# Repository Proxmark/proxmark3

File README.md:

# proxmark3: the official Proxmark repository!

The proxmark3 is a powerful general purpose RFID tool, the size of a deck
of cards, designed to snoop, listen and emulate everything from
**Low Frequency (125kHz)** to **High Frequency (13.56MHz)** tags.

This repository contains enough software, logic (for the FPGA), and design
documentation for the hardware that you could, at least in theory,
do something useful with a proxmark3.

## Resources

* [This repository!](https://github.com/Proxmark/proxmark3)
* [The Wiki](https://github.com/Proxmark/proxmark3/wiki)
* [The GitHub Pages website](http://proxmark.github.io/proxmark3/)
* [The Forum](http://www.proxmark.org/forum)
* The IRC channel: irc.freenode.org #proxmark3 ([chat in your browser](http://webchat.freenode.net/?channels=#proxmark3))
* [The Homebrew formula repository](https://github.com/Proxmark/homebrew-proxmark3)
* [Proxmark3 community discord server](https://discord.gg/86VcRtS)
   
## Development

The tools required to build  or run the project will vary depending on
your operating system. Please refer to [the wiki](https://github.com/Proxmark/proxmark3/wiki) for details.

## Obtaining hardware

The Proxmark3 is available for purchase (assembled and tested) from the
following locations:

| Distributor Name | Warehouse Location | Entity Location |
|------------------|--------------------|-----------------|
| [RyscCorp](https://proxmark3.com/)         | USA                | USA             |
| [Hackerwarehouse](https://hackerwarehouse.com/)  | USA                | USA             |
| [Elechouse](http://www.elechouse.com/)        | HK                 | HK              |
| [Lab401](https://lab401.com/)           | EU                 | HK              |
| [RFxSecure](http://www.rfxsecure.com/)       | CN                 | SG              |
| [Sneaktechnology](https://www.sneaktechnology.com/)  | CN                 | CN              |

Most of the ultra-low-volume contract assemblers could put
something like this together with a reasonable yield. A run of around
a dozen units is probably cost-effective. The BOM includes (possibly-
outdated) component pricing, and everything is available from Digikey
and the usual distributors.

If you've never assembled a modern circuit board by hand, then this is
not a good place to start. Some of the components (e.g. the crystals)
must not be assembled with a soldering iron, and require hot air.

The schematics are included; the component values given are not
necessarily correct for all situations, but it should be possible to do
nearly anything you would want with appropriate population options.

The printed circuit board artwork is also available, as Gerbers and an
Excellon drill file.

## License

This program is free software; you can redistribute it and/or modify
it under the terms of the GNU General Public License as published by
the Free Software Foundation; either version 2 of the License, or
(at your option) any later version.

This program is distributed in the hope that it will be useful,
but WITHOUT ANY WARRANTY; without even the implied warranty of
MERCHANTABILITY or FITNESS FOR A PARTICULAR PURPOSE.  See the
GNU General Public License for more details.

You should have received a copy of the GNU General Public License
along with this program; if not, write to the Free Software
Foundation, Inc., 51 Franklin St, Fifth Floor, Boston, MA  02110-1301  USA

Jonathan Westhues
user jwesthues, at host cq.cx

May 2007, Cambridge MA

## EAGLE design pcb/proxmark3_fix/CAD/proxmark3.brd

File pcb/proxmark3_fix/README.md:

Corrected Eagle layout files and re-generated CAM files. DRC checked (via eurocircuits.com 's PCB visualizer too) no problems found, ready to production!

Please find the change list in the CAD folder text file.

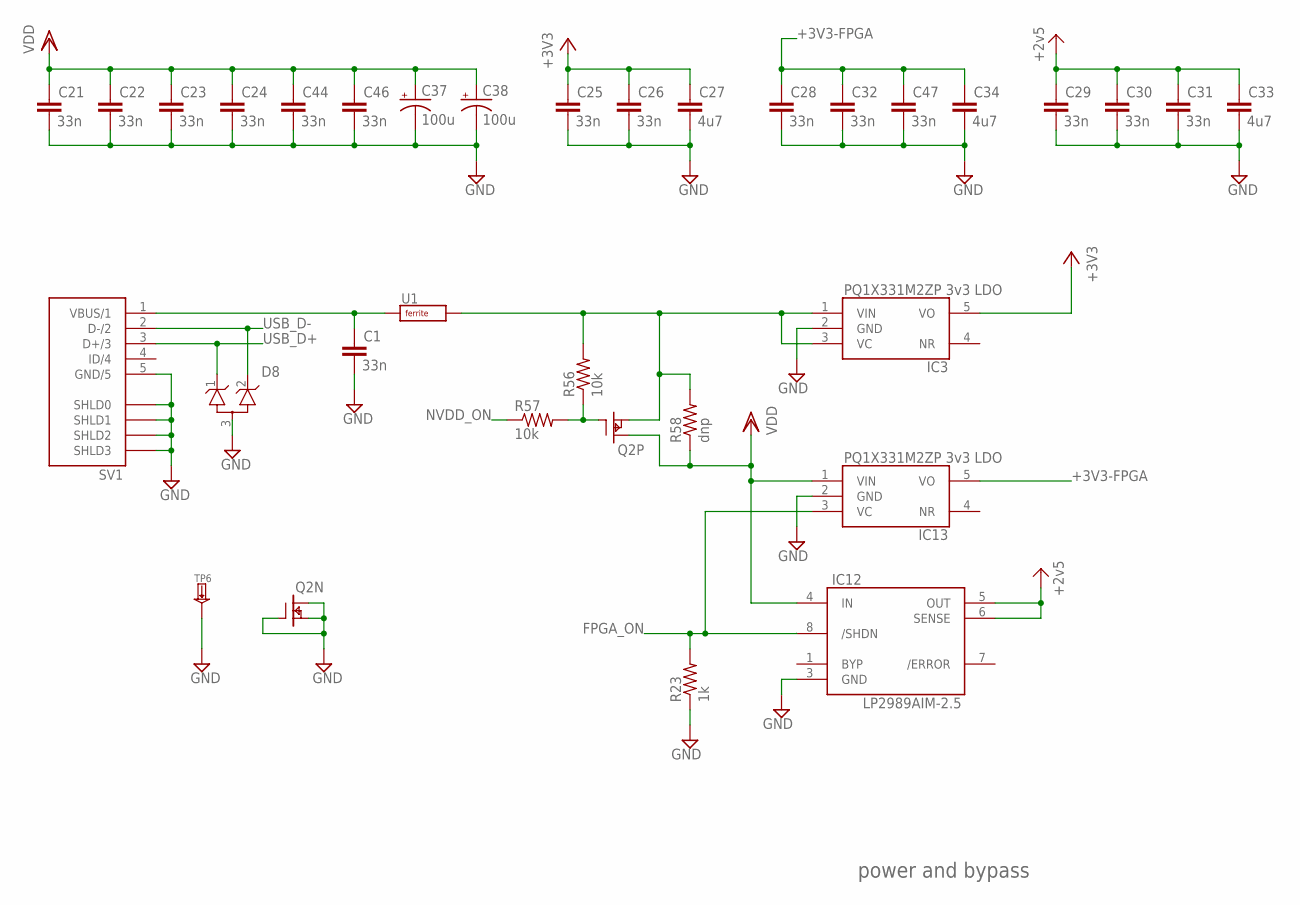
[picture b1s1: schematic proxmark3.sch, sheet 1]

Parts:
C1, C21, C22, C23, C24, C25, C26, C28, C29, C30, C31, C32, C44, C46, C47: 33n; RLC_0603
C27, C33, C34: 4u7; RLC_1210
C37, C38: 100u; CAPCAITOR-ELECTROLYTIC-ALCHIP-MZA-F80
D8: --MERGED_DUAL-TVS-COMMON-ANODE; --MERGED_SOT23-3LEAD
IC3, IC13: --MERGED_PQ1X331M2ZP-3V3-LDO-SOT-23-5; --MERGED_SOT-23-5
IC12: LP2989AIM-2.5; SOIC-8
Q2: IRF7307; SOIC-8
R23: 1k; RLC_0603
R56, R57: 10k; RLC_0603
R58: dnp; RLC_0603
SV1: USB-MINIB; USB-MINIB-SMD
TP6: TESTPADKEYSTONE-PTH; KEYSTONE-PTH-TESTPOINT-5011
U1: FERRITE0805; RLC_0805

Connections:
+2V5: C29.1, C30.1, C31.1, C33.1, IC12.5 (OUT), IC12.6 (SENSE); also elsewhere on the board
+3V3: C25.1, C26.1, C27.1, IC3.5 (VO); also elsewhere on the board
+3V3-FPGA: C28.1, C32.1, C34.1, C47.1, IC13.5 (VO); also elsewhere on the board
FPGA_ON: IC12.8 (/SHDN), IC13.3 (VC), R23.2; also elsewhere on the board
GND: C1.2, C21.2, C22.2, C23.2, C24.2, C25.2, C26.2, C27.2, C28.2, C29.2, C30.2, C31.2, C32.2, C33.2, C34.2, C37.-, C38.-, C44.2, C46.2, C47.2, D8.3 (A), IC3.2 (GND), IC12.3 (GND), IC13.2 (GND), Q2.1 (S), Q2.2 (G), Q2.8 (D), R23.1, SV1.5 (GND/5), SV1.TAB0 (SHLD0), SV1.TAB1 (SHLD1), SV1.TAB2 (SHLD2), SV1.TAB3 (SHLD3), TP6.A; also elsewhere on the board
unnamed: C1.1, SV1.1 (VBUS/1), U1.1 (A)
unnamed: IC3.1 (VIN), IC3.3 (VC), Q2.3 (S), R56.2, R58.2, U1.2 (B)
NVDD_ON: R57.1; also elsewhere on the board
PFETGATE: Q2.4 (G), R56.1, R57.2
USB_D+: D8.1 (K1), SV1.3 (D+/3); also elsewhere on the board
USB_D-: D8.2 (K2), SV1.2 (D-/2); also elsewhere on the board
VDD: C21.1, C22.1, C23.1, C24.1, C37.+, C38.+, C44.1, C46.1, IC12.4 (IN), IC13.1 (VIN), Q2.6 (D), R58.1; also elsewhere on the board

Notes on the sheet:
power and bypass

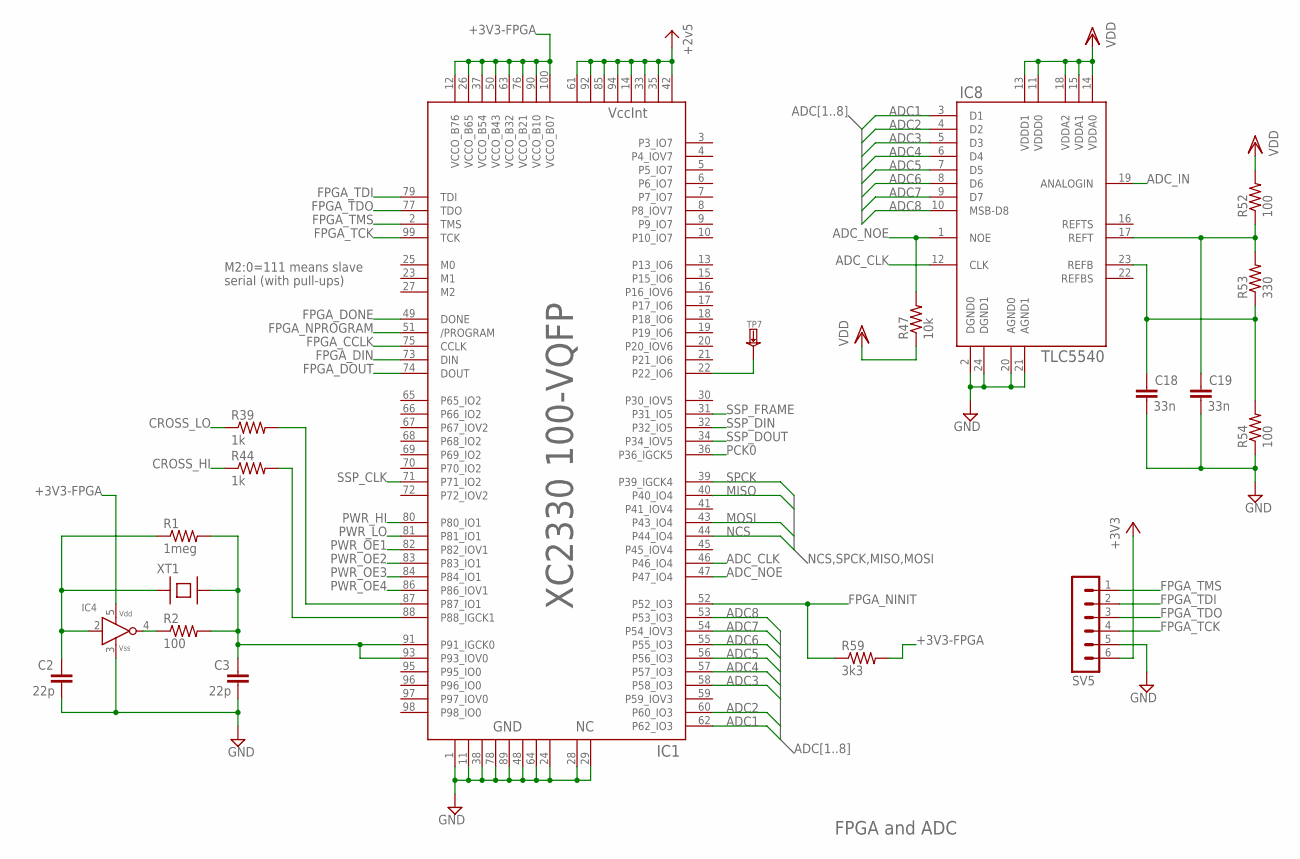
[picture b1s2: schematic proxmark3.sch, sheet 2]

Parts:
C2, C3: 22p; RLC_0603
C18, C19: 33n; RLC_0603
IC1: SPARTAN-II-XC2S30-100-VQFP; VQFP-100
IC4: HCU-INVERTER; SMV-5
IC8: TLC5540; TSSOP-24
R1: 1meg; RLC_0603
R2, R52, R54: 100; RLC_0603
R39, R44: 1k; RLC_0603
R47: 10k; RLC_0603
R53: 330; RLC_0603
R59: 3k3; RLC_0603
SV5: --MERGED_HEADER-MALE-6X1; --MERGED_HEADER-MALE-6X1-0.100-UNKEYED
TP7: TESTPADKEYSTONE-SMD; KEYSTONE-SMD-TESTPOINT-5015
XT1: XTAL-SMD-CITIZEN-CS10

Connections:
+2V5: IC1.14 (VCCINT5), IC1.33 (VCCINT6), IC1.35 (VCCINT7), IC1.42 (VCCINT8), IC1.61 (VCCINT1), IC1.85 (VCCINT3), IC1.92 (VCCINT2), IC1.94 (VCCINT4); also elsewhere on the board
+3V3: SV5.6; also elsewhere on the board
+3V3-FPGA: IC1.12 (VCCO_B76), IC1.26 (VCCO_B65), IC1.37 (VCCO_B54), IC1.50 (VCCO_B43), IC1.63 (VCCO_B32), IC1.76 (VCCO_B21), IC1.90 (VCCO_B10), IC1.100 (VCCO_B07), IC4.5 (VDD), R59.2; also elsewhere on the board
ADC1: IC1.62 (P62_IO3), IC8.3 (D1)
ADC2: IC1.60 (P60_IO3), IC8.4 (D2)
ADC3: IC1.58 (P58_IO3), IC8.5 (D3)
ADC4: IC1.57 (P57_IO3), IC8.6 (D4)
ADC5: IC1.56 (P56_IO3), IC8.7 (D5)
ADC6: IC1.55 (P55_IO3), IC8.8 (D6)
ADC7: IC1.54 (P54_IOV3), IC8.9 (D7)
ADC8: IC1.53 (P53_IO3), IC8.10 (MSB-D8)
ADC_CLK: IC1.46 (P46_IO4), IC8.12 (CLK)
ADC_IN: IC8.19 (ANALOGIN); also elsewhere on the board
ADC_NOE: IC1.47 (P47_IO4), IC8.1 (NOE), R47.2
CROSS_HI: R44.1; also elsewhere on the board
CROSS_LO: R39.1; also elsewhere on the board
FPGA_CCLK: IC1.75 (CCLK); also elsewhere on the board
FPGA_DIN: IC1.73 (DIN); also elsewhere on the board
FPGA_DONE: IC1.49 (DONE); also elsewhere on the board
FPGA_DOUT: IC1.74 (DOUT); also elsewhere on the board
FPGA_NINIT: IC1.52 (P52_IO3), R59.1; also elsewhere on the board
FPGA_NPROGRAM: IC1.51 (/PROGRAM); also elsewhere on the board
FPGA_TCK: IC1.99 (TCK), SV5.4
FPGA_TDI: IC1.79 (TDI), SV5.2
FPGA_TDO: IC1.77 (TDO), SV5.3
FPGA_TMS: IC1.2 (TMS), SV5.1
GND: C2.2, C3.2, C18.2, C19.2, IC1.1 (GND1), IC1.11 (GND2), IC1.24 (GND8), IC1.28 (NC0), IC1.29 (NC1), IC1.38 (GND3), IC1.48 (GND6), IC1.64 (GND7), IC1.78 (GND4), IC1.89 (GND5), IC4.3 (VSS), IC8.2 (DGND0), IC8.20 (AGND0), IC8.21 (AGND1), IC8.24 (DGND1), R54.1, SV5.5; also elsewhere on the board
MISO: IC1.40 (P40_IO4); also elsewhere on the board
MOSI: IC1.43 (P43_IO4); also elsewhere on the board
unnamed: IC4.4 (Y), R2.1
unnamed: C2.1, IC4.2 (A), R1.1, XT1.A
unnamed: C3.1, IC1.91 (P91_IGCK0), IC1.93 (P93_IOV0), R1.2, R2.2, XT1.B
unnamed: C18.1, IC8.23 (REFB), R53.1, R54.2
unnamed: IC1.87 (P87_IO1), R39.2
unnamed: IC1.88 (P88_IGCK1), R44.2
unnamed: C19.1, IC8.17 (REFT), R52.1, R53.2
unnamed: IC1.22 (P22_IO6), TP7.1
NCS: IC1.44 (P44_IO4); also elsewhere on the board
PCK0: IC1.36 (P36_IGCK5); also elsewhere on the board
PWR_HI: IC1.80 (P80_IO1); also elsewhere on the board
PWR_LO: IC1.81 (P81_IO1); also elsewhere on the board
PWR_OE1: IC1.82 (P82_IOV1); also elsewhere on the board
PWR_OE2: IC1.83 (P83_IO1); also elsewhere on the board
PWR_OE3: IC1.84 (P84_IO1); also elsewhere on the board
PWR_OE4: IC1.86 (P86_IOV1); also elsewhere on the board
SPCK: IC1.39 (P39_IGCK4); also elsewhere on the board
SSP_CLK: IC1.71 (P71_IO2); also elsewhere on the board
SSP_DIN: IC1.32 (P32_IO5); also elsewhere on the board
SSP_DOUT: IC1.34 (P34_IOV5); also elsewhere on the board
SSP_FRAME: IC1.31 (P31_IO5); also elsewhere on the board
VDD: IC8.11 (VDDD0), IC8.13 (VDDD1), IC8.14 (VDDA0), IC8.15 (VDDA1), IC8.18 (VDDA2), R47.1, R52.2; also elsewhere on the board

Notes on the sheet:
FPGA and ADC
M2:0=111 means slave
serial (with pull-ups)

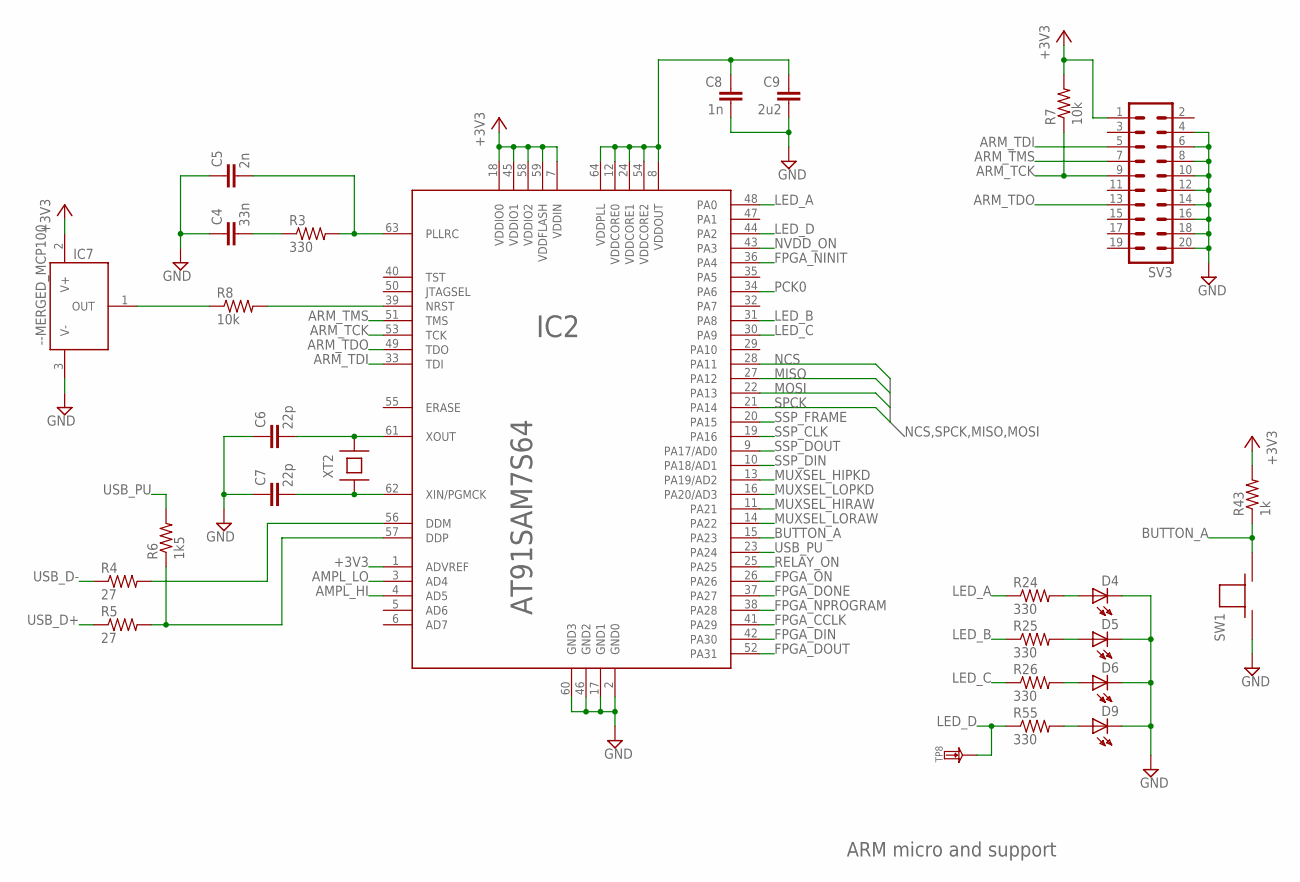
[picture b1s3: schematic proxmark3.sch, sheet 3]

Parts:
C4: 33n; RLC_0603
C5: 2n; RLC_0603
C6, C7: 22p; --MERGED_RLC_0603
C8: 1n; RLC_0603
C9: 2u2; RLC_1210
D4, D5, D6, D9: LED; LED_0603
IC2: AT91SAM7S64; LQFP-64
IC7: --MERGED_MCP100; --MERGED_SOT23-3LEAD
R3, R24, R25, R26, R55: 330; RLC_0603
R4, R5: 27; RLC_0603
R6: 1k5; RLC_0603
R7, R8: 10k; RLC_0603
R43: 1k; RLC_0603
SV3: HEADER-MALE-10X2; HEADER-MALE-10X2-0.100-SHROUDED
SW1: TACTSWITCH; TACTSWITCH-SMD-EVQQ1
TP8: TESTPADKEYSTONE-SMD; KEYSTONE-SMD-TESTPOINT-5015
XT2: XTAL-SMD-CITIZEN-CS10

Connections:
+3V3: IC2.1 (ADVREF), IC2.7 (VDDIN), IC2.18 (VDDIO0), IC2.45 (VDDIO1), IC2.58 (VDDIO2), IC2.59 (VDDFLASH), IC7.2 (V+), R7.2, R43.2, SV3.1; also elsewhere on the board
AMPL_HI: IC2.4 (AD5); also elsewhere on the board
AMPL_LO: IC2.3 (AD4); also elsewhere on the board
ARM_TCK: IC2.53 (TCK), R7.1, SV3.9
ARM_TDI: IC2.33 (TDI), SV3.5
ARM_TDO: IC2.49 (TDO), SV3.13
ARM_TMS: IC2.51 (TMS), SV3.7
BUTTON_A: IC2.15 (PA23), R43.1, SW1.B
FPGA_CCLK: IC2.41 (PA29); also elsewhere on the board
FPGA_DIN: IC2.42 (PA30); also elsewhere on the board
FPGA_DONE: IC2.37 (PA27); also elsewhere on the board
FPGA_DOUT: IC2.52 (PA31); also elsewhere on the board
FPGA_NINIT: IC2.36 (PA4); also elsewhere on the board
FPGA_NPROGRAM: IC2.38 (PA28); also elsewhere on the board
FPGA_ON: IC2.26 (PA26); also elsewhere on the board
GND: C4.1, C5.1, C6.1, C7.1, C8.2, C9.2, D4.- (C), D5.- (C), D6.- (C), D9.- (C), IC2.2 (GND0), IC2.17 (GND1), IC2.46 (GND2), IC2.60 (GND3), IC7.3 (V-), SV3.4, SV3.6, SV3.8, SV3.10, SV3.12, SV3.14, SV3.16, SV3.18, SV3.20, SW1.A; also elsewhere on the board
LED_A: IC2.48 (PA0), R24.1
LED_B: IC2.31 (PA8), R25.1
LED_C: IC2.30 (PA9), R26.1
LED_D: IC2.44 (PA2), R55.1, TP8.1
MISO: IC2.27 (PA12); also elsewhere on the board
MOSI: IC2.22 (PA13); also elsewhere on the board
MUXSEL_HIPKD: IC2.13 (PA19/AD2); also elsewhere on the board
MUXSEL_HIRAW: IC2.11 (PA21); also elsewhere on the board
MUXSEL_LOPKD: IC2.16 (PA20/AD3); also elsewhere on the board
MUXSEL_LORAW: IC2.14 (PA22); also elsewhere on the board
unnamed: C5.2, IC2.63 (PLLRC), R3.2
unnamed: C4.2, R3.1
unnamed: C6.2, IC2.61 (XOUT), XT2.B
unnamed: C7.2, IC2.62 (XIN/PGMCK), XT2.A
unnamed: IC2.39 (NRST), R8.2
unnamed: C8.1, C9.1, IC2.8 (VDDOUT), IC2.12 (VDDCORE0), IC2.24 (VDDCORE1), IC2.54 (VDDCORE2), IC2.64 (VDDPLL)
unnamed: IC2.56 (DDM), R4.2
unnamed: IC2.57 (DDP), R5.2, R6.1
unnamed: IC7.1 (OUT), R8.1
unnamed: D9.+ (A), R55.2
unnamed: D6.+ (A), R26.2
unnamed: D5.+ (A), R25.2
unnamed: D4.+ (A), R24.2
NCS: IC2.28 (PA11); also elsewhere on the board
NVDD_ON: IC2.43 (PA3); also elsewhere on the board
PCK0: IC2.34 (PA6); also elsewhere on the board
RELAY_ON: IC2.25 (PA25); also elsewhere on the board
SPCK: IC2.21 (PA14); also elsewhere on the board
SSP_CLK: IC2.19 (PA16); also elsewhere on the board
SSP_DIN: IC2.10 (PA18/AD1); also elsewhere on the board
SSP_DOUT: IC2.9 (PA17/AD0); also elsewhere on the board
SSP_FRAME: IC2.20 (PA15); also elsewhere on the board
USB_D+: R5.1; also elsewhere on the board
USB_D-: R4.1; also elsewhere on the board
USB_PU: IC2.23 (PA24), R6.2

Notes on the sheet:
ARM micro and support

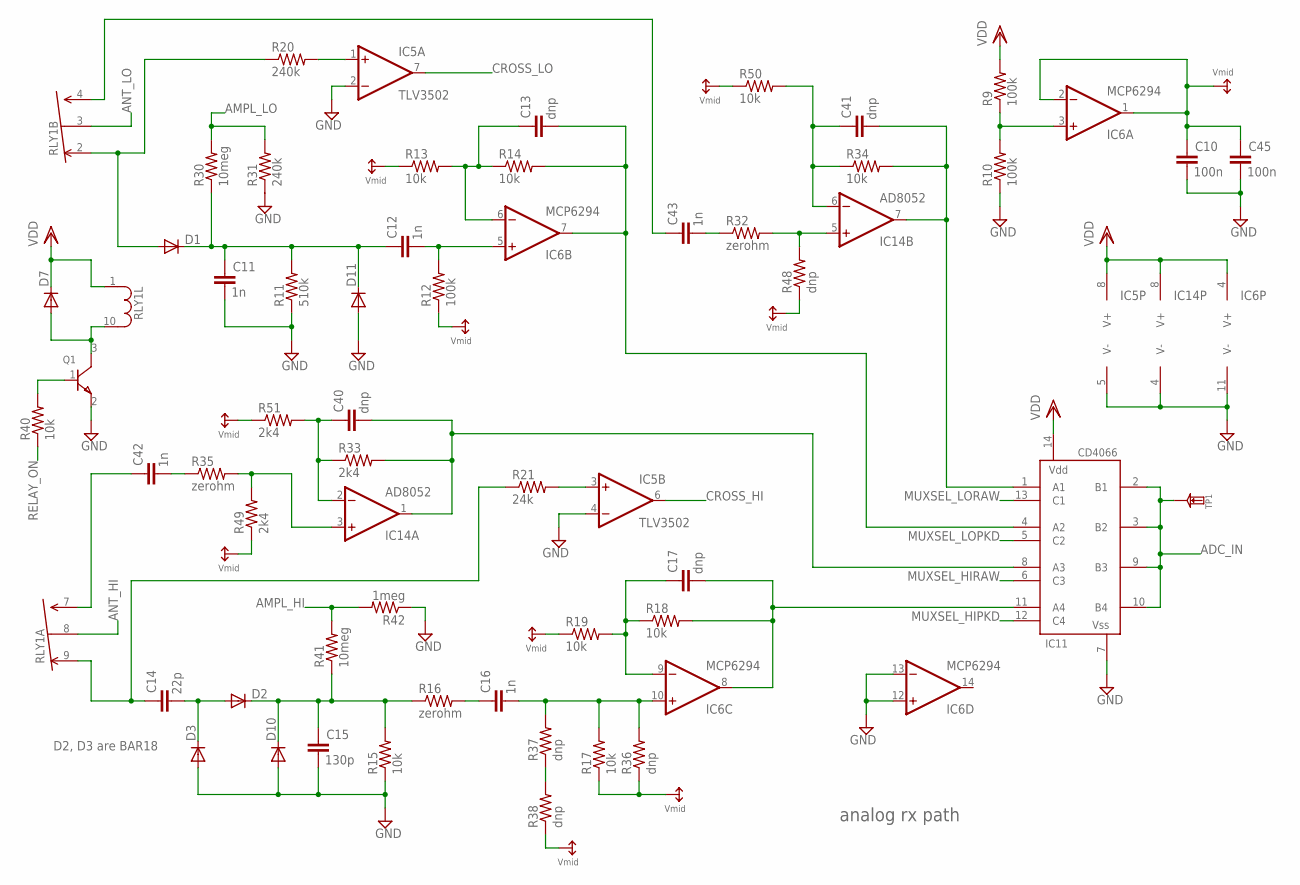
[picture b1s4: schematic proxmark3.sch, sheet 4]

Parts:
C10, C45: 100n; RLC_0603
C11, C12, C16, C42, C43: 1n; RLC_0603
C13, C17, C40, C41: dnp; RLC_0603
C14: 22p; RLC_0603
C15: 130p; RLC_0603
D1, D2, D3, D7, D10, D11: --MERGED_DIODE-SMD-SOT23; --MERGED_SOT23-3LEAD
IC5: TLV3502; SOT-23-8-OR-MSOP-8
IC6: MCP6294; TSSOP-14
IC11: CD4066; TSSOP-14
IC14: AD8052; MSOP8
Q1: --MERGED_NPN-SOT23-2N3904; --MERGED_SOT23-3LEAD
R9, R10, R12: 100k; RLC_0603
R11: 510k; RLC_0603
R13, R14, R15, R17, R18, R19, R34, R40, R50: 10k; RLC_0603
R16, R32, R35: zerohm; RLC_0603
R20, R31: 240k; RLC_0603
R21: 24k; RLC_0603
R30, R41: 10meg; RLC_0603
R33, R49, R51: 2k4; RLC_0603
R36, R37, R38, R48: dnp; RLC_0603
R42: 1meg; RLC_0603
RLY1: --MERGED_RELAY-DPDT; --MERGED_TQ-SMD-RELAY
TP1: TESTPADKEYSTONE-SMD; KEYSTONE-SMD-TESTPOINT-5015

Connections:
ADCDR_HI: C17.2, IC6.8 (OUT), IC11.11 (A4), R18.2
ADCDR_LO: C13.2, IC6.7 (OUT), IC11.4 (A2), R14.2
ADC_IN: IC11.2 (B1), IC11.3 (B2), IC11.9 (B3), IC11.10 (B4), TP1.1; also elsewhere on the board
AMPL_HI: R41.2, R42.2; also elsewhere on the board
AMPL_LO: R30.2, R31.2; also elsewhere on the board
ANT_HI: RLY1.8 (COM); also elsewhere on the board
ANT_LO: RLY1.3 (COM); also elsewhere on the board
CROSS_HI: IC5.6 (OUT); also elsewhere on the board
CROSS_LO: IC5.7 (OUT); also elsewhere on the board
GND: C10.2, C11.2, C15.2, C45.2, D3.1 (A), D10.1 (A), D11.1 (A), IC5.2 (-IN), IC5.4 (-IN), IC5.5 (V-), IC6.11 (V-), IC6.12 (+IN), IC6.13 (-IN), IC11.7 (VSS), IC14.4 (V-), Q1.2 (E), R10.1, R11.1, R15.1, R31.1, R42.1; also elsewhere on the board
MUXSEL_HIPKD: IC11.12 (C4); also elsewhere on the board
MUXSEL_HIRAW: IC11.6 (C3); also elsewhere on the board
MUXSEL_LOPKD: IC11.5 (C2); also elsewhere on the board
MUXSEL_LORAW: IC11.13 (C1); also elsewhere on the board
unnamed: IC6.3 (+IN), R9.1, R10.2
unnamed: C17.1, IC6.9 (-IN), R18.1, R19.2
unnamed: C12.2, IC6.5 (+IN), R12.2
unnamed: C13.1, IC6.6 (-IN), R13.2, R14.1
unnamed: C16.1, R16.2
unnamed: C11.1, C12.1, D1.3 (C), D11.3 (C), R11.2, R30.1
unnamed: C14.2, D2.1 (A), D3.3 (C)
unnamed: C15.1, D2.3 (C), D10.3 (C), R15.2, R16.1, R41.1
unnamed: C16.2, IC6.10 (+IN), R17.2, R36.2, R37.2
unnamed: IC5.1 (+IN), R20.2
unnamed: IC5.3 (+IN), R21.2
unnamed: D7.1 (A), Q1.3 (C), RLY1.10
unnamed: C14.1, R21.1, RLY1.9 (NC)
unnamed: C42.1, RLY1.7 (NO)
unnamed: Q1.1 (B), R40.2
unnamed: D1.1 (A), R20.1, RLY1.2 (NC)
unnamed: C41.2, IC11.1 (A1), IC14.7 (OUT), R34.2
unnamed: C43.1, RLY1.4 (NO)
unnamed: IC14.3 (+IN), R35.2, R49.2
unnamed: C43.2, R32.1
unnamed: C42.2, R35.1
unnamed: C40.1, IC14.2 (-IN), R33.1, R51.2
unnamed: C41.1, IC14.6 (-IN), R34.1, R50.2
unnamed: IC14.5 (+IN), R32.2, R48.2
unnamed: R37.1, R38.2
RAW_HI: C40.2, IC11.8 (A3), IC14.1 (OUT), R33.2
RELAY_ON: R40.1; also elsewhere on the board
VDD: D7.3 (C), IC5.8 (V+), IC6.4 (V+), IC11.14 (VDD), IC14.8 (V+), R9.2, RLY1.1; also elsewhere on the board
VMID: C10.1, C45.1, IC6.1 (OUT), IC6.2 (-IN), R12.1, R13.1, R17.1, R19.1, R36.1, R38.1, R48.1, R49.1, R50.1, R51.1

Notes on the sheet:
analog rx path
D2, D3 are BAR18

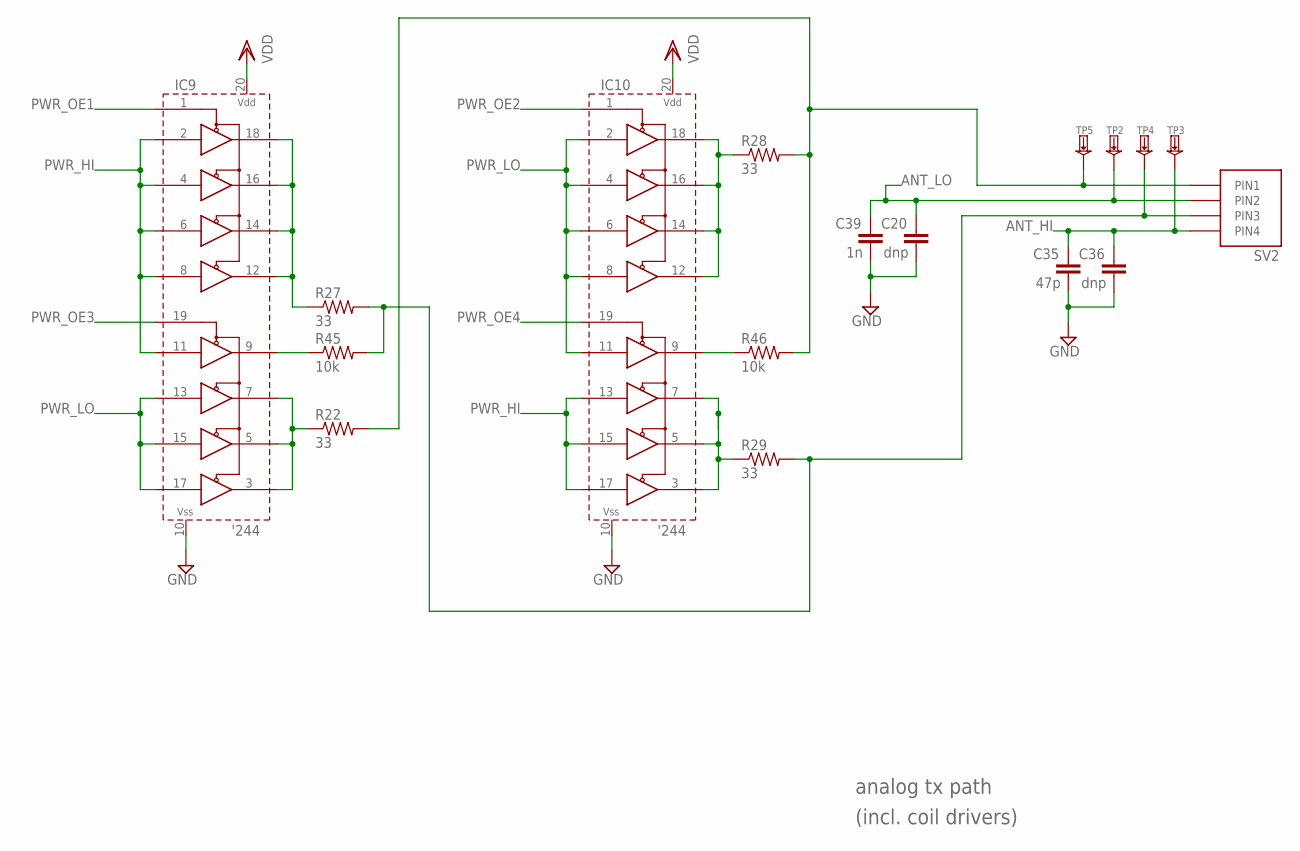
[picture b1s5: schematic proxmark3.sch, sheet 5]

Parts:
C20, C36: dnp; RLC_0603
C35: 47p; RLC_0603
C39: 1n; RLC_0603
IC9, IC10: 74XX244-OCTAL-TRISTATE-BUFFERS; TSSOP-20
R22, R27, R28, R29: 33; RLC_0603
R45, R46: 10k; RLC_0603
SV2: HIROSE-MQ172-4POS
TP2, TP3, TP4, TP5: TESTPADKEYSTONE-SMD; KEYSTONE-SMD-TESTPOINT-5015

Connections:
ANT_HI: C35.1, C36.1, SV2.4 (PIN4), TP3.1; also elsewhere on the board
ANT_LO: C20.1, C39.1, SV2.2 (PIN2), TP2.1; also elsewhere on the board
GND: C20.2, C35.2, C36.2, C39.2, IC9.10 (VSS), IC10.10 (VSS); also elsewhere on the board
unnamed: R27.2, R29.2, R45.2, SV2.3 (PIN3), TP4.1
unnamed: R22.2, R28.2, R46.2, SV2.1 (PIN1), TP5.1
unnamed: IC9.12 (1Y4), IC9.14 (1Y3), IC9.16 (1Y2), IC9.18 (1Y1), R27.1
unnamed: IC10.12 (1Y4), IC10.14 (1Y3), IC10.16 (1Y2), IC10.18 (1Y1), R28.1
unnamed: IC9.3 (2Y4), IC9.5 (2Y3), IC9.7 (2Y2), R22.1
unnamed: IC10.3 (2Y4), IC10.5 (2Y3), IC10.7 (2Y2), R29.1
unnamed: IC9.9 (2Y1), R45.1
unnamed: IC10.9 (2Y1), R46.1
PWR_HI: IC9.2 (1A1), IC9.4 (1A2), IC9.6 (1A3), IC9.8 (1A4), IC9.11 (2A1), IC10.13 (2A2), IC10.15 (2A3), IC10.17 (2A4); also elsewhere on the board
PWR_LO: IC9.13 (2A2), IC9.15 (2A3), IC9.17 (2A4), IC10.2 (1A1), IC10.4 (1A2), IC10.6 (1A3), IC10.8 (1A4), IC10.11 (2A1); also elsewhere on the board
PWR_OE1: IC9.1 (1NOE); also elsewhere on the board
PWR_OE2: IC10.1 (1NOE); also elsewhere on the board
PWR_OE3: IC9.19 (2NOE); also elsewhere on the board
PWR_OE4: IC10.19 (2NOE); also elsewhere on the board
VDD: IC9.20 (VDD), IC10.20 (VDD); also elsewhere on the board

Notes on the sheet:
analog tx path
(incl. coil drivers)

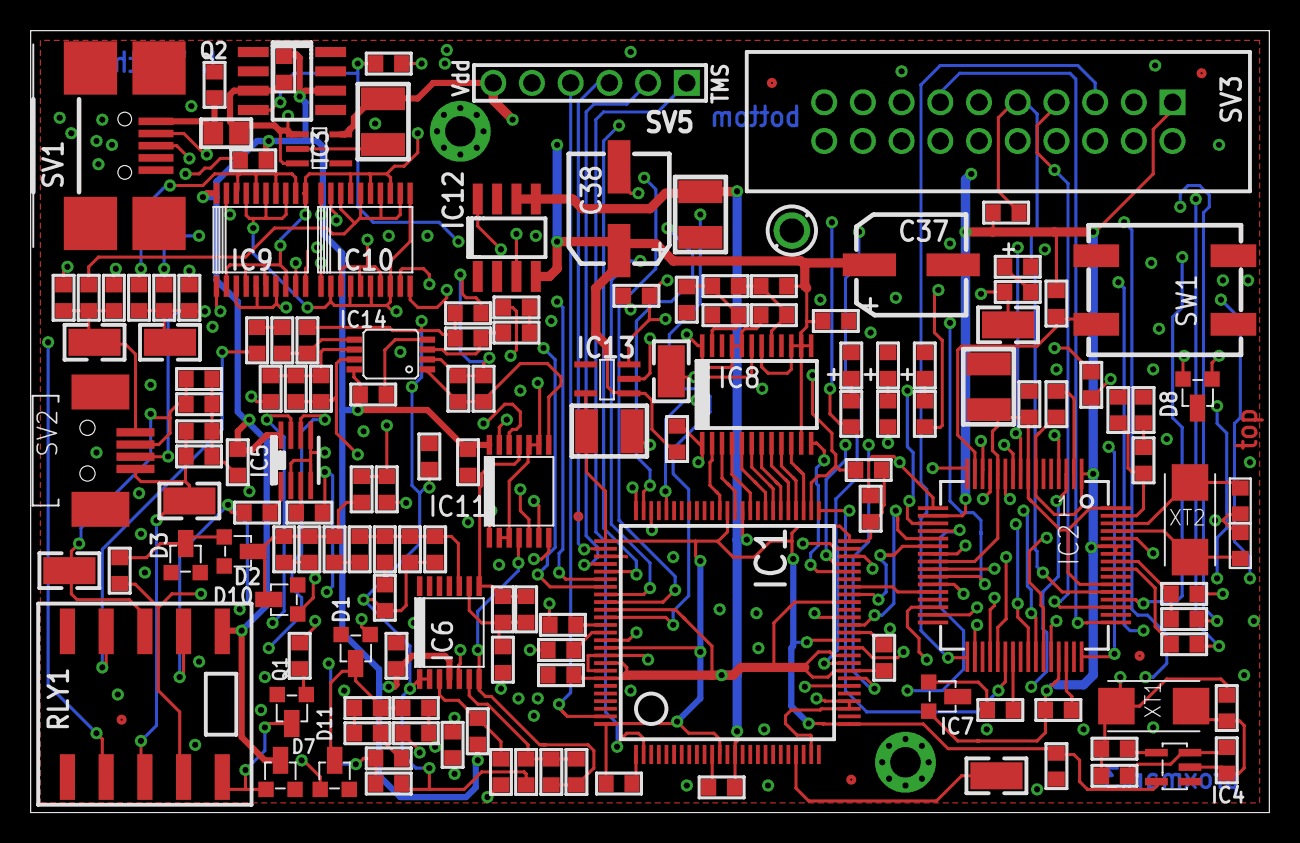
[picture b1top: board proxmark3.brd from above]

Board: 4 copper layers, 81.3 x 51.3 mm, 150 parts (0 on the bottom side), 127 nets.

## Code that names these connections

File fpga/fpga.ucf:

# See the schematic for the pin assignment.

NET "adc_d<0>"  LOC = "P62"  ;
NET "adc_d<1>"  LOC = "P60"  ;
NET "adc_d<2>"  LOC = "P58"  ;
NET "adc_d<3>"  LOC = "P57"  ;
NET "adc_d<4>"  LOC = "P56"  ;
NET "adc_d<5>"  LOC = "P55"  ;
NET "adc_d<6>"  LOC = "P54"  ;
NET "adc_d<7>"  LOC = "P53"  ;
NET "cross_hi"  LOC = "P88"  ;
#NET "miso"      LOC = "P40"  ;
#PACE: Start of Constraints generated by PACE

#PACE: Start of PACE I/O Pin Assignments
NET "adc_clk"  LOC = "P46"  ;
NET "adc_noe"  LOC = "P47"  ;
NET "ck_1356meg"  LOC = "P91"  ;
NET "ck_1356megb"  LOC = "P93"  ;
NET "cross_lo"  LOC = "P87"  ;
NET "dbg"  LOC = "P22"  ;
NET "mosi"  LOC = "P43"  ;
NET "ncs"  LOC = "P44"  ;
NET "pck0"  LOC = "P36"  ;
NET "pwr_hi"  LOC = "P80"  ;
NET "pwr_lo"  LOC = "P81"  ;
NET "pwr_oe1"  LOC = "P82"  ;
NET "pwr_oe2"  LOC = "P83"  ;
NET "pwr_oe3"  LOC = "P84"  ;
NET "pwr_oe4"  LOC = "P86"  ;
NET "spck"  LOC = "P39"  ;
NET "ssp_clk"  LOC = "P71"  ;
NET "ssp_din"  LOC = "P32"  ;
NET "ssp_dout"  LOC = "P34"  ;
NET "ssp_frame"  LOC = "P31"  ;

#PACE: Start of PACE Area Constraints

#PACE: Start of PACE Prohibit Constraints

#PACE: End of Constraints generated by PACE

# definition of Clock nets:
NET "ck_1356meg" TNM_NET = "clk_net_1356" ;
NET "ck_1356megb" TNM_NET = "clk_net_1356b" ;
NET "pck0" TNM_NET = "clk_net_pck0" ;
NET "spck" TNM_NET = "clk_net_spck" ;

# Timing specs of clock nets:
TIMEGRP "clk_net_1356_all" = "clk_net_1356" "clk_net_1356b" ;
TIMESPEC "TS_1356MHz" = PERIOD "clk_net_1356_all" 74 ns HIGH 37 ns ;
TIMESPEC "TS_24MHz" = PERIOD "clk_net_pck0" 42 ns HIGH 21 ns ;
TIMESPEC "TS_4MHz" = PERIOD "clk_net_spck" 250 ns HIGH 125 ns ;

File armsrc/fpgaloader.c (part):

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void SetupSpi(int mode)
{
	// PA10 -> SPI_NCS2 chip select (LCD)
	// PA11 -> SPI_NCS0 chip select (FPGA)
	// PA12 -> SPI_MISO Master-In Slave-Out
	// PA13 -> SPI_MOSI Master-Out Slave-In
	// PA14 -> SPI_SPCK Serial Clock

	// Disable PIO control of the following pins, allows use by the SPI peripheral
	AT91C_BASE_PIOA->PIO_PDR =
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		GPIO_NCS2   |
		GPIO_MISO   |
		GPIO_MOSI   |
		GPIO_SPCK;

	AT91C_BASE_PIOA->PIO_ASR =
		GPIO_NCS0   |
		GPIO_MISO   |
		GPIO_MOSI   |
		GPIO_SPCK;

	AT91C_BASE_PIOA->PIO_BSR = GPIO_NCS2;

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		case SPI_FPGA_MODE:
			AT91C_BASE_SPI->SPI_MR =
				( 0 << 24)  |   // Delay between chip selects (take default: 6 MCK periods)
				(14 << 16)  |   // Peripheral Chip Select (selects FPGA SPI_NCS0 or PA11)
				( 0 << 7)   |   // Local Loopback Disabled
				( 1 << 4)   |   // Mode Fault Detection disabled
				( 0 << 2)   |   // Chip selects connected directly to peripheral
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
static void DownloadFPGA_byte(unsigned char w)
{
#define SEND_BIT(x) { if(w & (1<<x) ) HIGH(GPIO_FPGA_DIN); else LOW(GPIO_FPGA_DIN); HIGH(GPIO_FPGA_CCLK); LOW(GPIO_FPGA_CCLK); }
	SEND_BIT(7);
	SEND_BIT(6);
	SEND_BIT(5);
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
	int i=0;

	AT91C_BASE_PIOA->PIO_OER = GPIO_FPGA_ON;
	AT91C_BASE_PIOA->PIO_PER = GPIO_FPGA_ON;
	HIGH(GPIO_FPGA_ON);     // ensure everything is powered on

	SpinDelay(50);

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
	// These pins are inputs
	AT91C_BASE_PIOA->PIO_ODR =
		GPIO_FPGA_NINIT |
		GPIO_FPGA_DONE;
	// PIO controls the following pins
	AT91C_BASE_PIOA->PIO_PER =
		GPIO_FPGA_NINIT |
		GPIO_FPGA_DONE;
	// Enable pull-ups
	AT91C_BASE_PIOA->PIO_PPUER =
		GPIO_FPGA_NINIT |
		GPIO_FPGA_DONE;

	// setup initial logic state
	HIGH(GPIO_FPGA_NPROGRAM);
	LOW(GPIO_FPGA_CCLK);
	LOW(GPIO_FPGA_DIN);
	// These pins are outputs
	AT91C_BASE_PIOA->PIO_OER =
		GPIO_FPGA_NPROGRAM  |
		GPIO_FPGA_CCLK      |
		GPIO_FPGA_DIN;

	// enter FPGA configuration mode
	LOW(GPIO_FPGA_NPROGRAM);
	SpinDelay(50);
	HIGH(GPIO_FPGA_NPROGRAM);

	i=100000;
	// wait for FPGA ready to accept data signal
	while ((i) && ( !(AT91C_BASE_PIOA->PIO_PDSR & GPIO_FPGA_NINIT ) ) ) {
		i--;
	}

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
	// continue to clock FPGA until ready signal goes high
	i=100000;
	while ( (i--) && ( !(AT91C_BASE_PIOA->PIO_PDSR & GPIO_FPGA_DONE ) ) ) {
		HIGH(GPIO_FPGA_CCLK);
		LOW(GPIO_FPGA_CCLK);
	}
	// crude error indicator, leave both red LEDs on and return
	if (i==0){
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void SetAdcMuxFor(uint32_t whichGpio)
{
	AT91C_BASE_PIOA->PIO_OER =
		GPIO_MUXSEL_HIPKD |
		GPIO_MUXSEL_LOPKD |
		GPIO_MUXSEL_LORAW |
		GPIO_MUXSEL_HIRAW;

	AT91C_BASE_PIOA->PIO_PER =
		GPIO_MUXSEL_HIPKD |
		GPIO_MUXSEL_LOPKD |
		GPIO_MUXSEL_LORAW |
		GPIO_MUXSEL_HIRAW;

	LOW(GPIO_MUXSEL_HIPKD);
	LOW(GPIO_MUXSEL_HIRAW);
	LOW(GPIO_MUXSEL_LORAW);
	LOW(GPIO_MUXSEL_LOPKD);

	HIGH(whichGpio);
}
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
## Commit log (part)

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2018-11-19 jsonloadstr
2018-11-19 cmdhficlass
2018-11-19 armsrc not compiled. fixed
2018-11-23 Get rid of polarssl (#717)
2018-11-25 Fido U2F complete (#716)
    * add pkwrite
    * asn1print
    * asn1dump and CA
    * added PrintAndLogEx for merge commits between repo easier than now
    * changelog
2018-11-26 Support TCP ports for proxmark
    On ChromeOS Linux apps can't access serial port but they can connect to TCP,
    so I wrote a simple app to forward TCP to serial. I suppose this can
    have other uses as well.
2018-11-30 jansson update. 2.11 to 2.12 (#724)
2018-11-30 Fix public key lenght to 65 bytes
2018-11-30 add tinycbor
2018-11-30 https://github.com/Proxmark/proxmark3/pull/725
2018-11-30 explain abbrevations
2018-12-03 Update hitagS.c
    Bugfix for #605 - wrong compare for tag.LKP
2018-12-03 Fix compilation error on OS X
2018-12-07 Added mifare trailer block decoding for sector commands
2018-12-07 LIBS to LIBINCLUDES
2019-01-01 Improved PCF 7931 read code and implemented a simple PCF7931 password bruteforce
2019-01-04 avoid compiler warning in client/cliparser/argtable3.c (#746)
2019-01-05 Fix PrintAndLogEx ERR
2019-01-06 Changed error detection to allow printing of single blocks on failure
2019-01-07 RDV4.0 Smartcard Slot Firmware Upgrade * new firmware in client/sc_upgrade_firmware directory * improved sc upgrade: * check SHA-512 of firmware file * search and find firmware file in predefined dir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
2019-01-12 fixing hf 15 * add hf list 15 * refactoring: move all of hf list code to cmdhflist.c
2019-01-12 Fix 15 snoop (#752)
    * fixing hf 15: implement hf 15 snoop
    * rename hf 15 record to hf 15 snoop
    * speedup sampling / decoding:
    * new FPGA mode FPGA_HF_READER_RX_XCORR_AMPLITUDE implements amplitude(ci, cq) on FPGA
    * inlining the decoders in iso15693.c
    * inlining memcpy/memset in LogTrace()
2019-01-14 adjust CI testscript for new emv commands
2019-01-16 Allow skipping or trying different keys in hf mf dump (#759)
2019-01-17 Add smartcard protocol T=0 (RRG repository PRs 71,72,74,75 by @merlokk) (#757)
2019-01-19 add missing include. Fix format string.
2019-01-21 Add ROCA vulnerability test (RRG repository PR 76 by @merlokk) (#762)
2019-01-28 Add support for standard USB Smartcard Readers (#765)
    * add PCSC interface (pcsc.c and pcsc.h)
    * new command 'sc select' to choose an USB Smartcard Reader
    * updated CI/.travis.yml accordingly
    * remove TCK CRC check in i2c.c It is done in PrintATR() anyway
    * Fix TCK CRC check in PrintATR()
    * Add PCSC reader support to 'sc info'
2019-01-30 Legic TagSim: increased reader timeout
    Bug reports from @raphCode and @uhei over at the
    RfidResearchGroup have shown that the tag to rwd
    timeout is too short.
2019-02-02 fido fix
2019-02-04 added SoloKey certificate
2019-02-06 Update list of Certificate Authorities Public Keys (source: https://www.eftlab.co.uk/index.php/site-map/knowledge-base/243-ca-public-keys) (#777)
    * allow tabs in client/emv/capk.txt
    * fix issue with printing RID and CSN of certificates
2019-02-09 emv/sc fixes and modifications: (#780)
    * print selected Smartcard Reader in PrintChannel()
    * implement 'sc sel <readername>'. Readername can include wildcards * and ?
    * fixing EMV APDU exchange (again)
    * use EMVExchangeEx() instead of EMVExchange() in fidocore.c
2019-02-09 fix endless loop (#782)
2019-02-16 Add raw HF signal plotting * new fpga module hi_get_trace.v - store A/D converter output to circular buffer on FPGA * new command 'hf plot' - pull data from FPGA and display it in Graph Window
2019-02-19 fix/add help and update CHANGELOG.md
2019-02-20 main merge
2019-02-20 fix ATR length * TS, T0, T[A-D][1-4], max. 15 HB, TCK = 34 Bytes
2019-02-26 add 14a apdu send framing (based on RRG repo PR86 by Merlokk)
2019-03-03 chip manufacturer and type identification: (#796)
    * add more manufacturers
    * refactor chipID decoding
    * move to separate file taginfo.[ch]
2019-03-13 fix hitag functions (issue #798) * ... and whitespace formating
2019-03-14 mad and ndef compiles
2019-03-14 mf ndef and mad
2019-03-15 Added some LED utility functions (#802)
2019-03-19 Ndef and MAD (#801)
    * move mifare stuff to separate folder
    * add mad and ndef
2019-03-24 iso14443b modifications (#804)
    * LED handling
    * improve 'hf plot' support
2019-03-27 fixed bug in CmdBiphaseDecodeRaw()
2019-04-08 fix hf mf sim * fix parity encryption (thanks to Eloff, http://www.proxmark.org/forum/viewtopic.php?id=6347) * add support to simulate Mifare Mini, Mifare 2K and Mifare 4K * change to standard LED ha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
2019-04-11 hf search: add support for Legic tags
2019-04-18 fix hf mf sim * use DMA to receive reader command * switch earlier from send to listen mode * move ADC initializer to iso14443_setup * remove remainders of incomplete Mifare 10Byte UID simulation * s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
2019-05-14 Add: new option 'd' in 'hf mf ekeyprn' to create dumpkeys.bin from emulator memory * whitespace
2019-05-22 Add: new option 'd' in 'hf mf ekeyprn' to create dumpkeys.bin from emulator memory (#822)
    (and whitespace fixes)
2019-05-27 add: Home (Pos1) and End key bindings in graph GUI (based on @mcd1992 change on RRG repo) (#823)
2019-05-29 Specify that we need TCP and not UDP connection
2019-06-12 add samples to skip lf config - & em 4x05 protect cmd
    add "samples to skip" for lf config (mainly for lf snoop)
    add lf em 4x05protect command to write protection on em4x05 chips
2019-06-16 T55xx downlink Modes
    Changes :
    - Added t55xx downlink protocols (long leading reference, leading 0 and 1 of 4)
    - Added function to all read to call differnet downlink functions (to match write)
    - Update functions to support using differnet downlink modes.
    - Added support for calling downlink modes for lf t55 read, write and detect
    - Added new function lf t55 bruteforcedl to support downlink modes as well as try each mode
2019-06-21 fix flags - only need 1 bit
2019-06-25 Resolved Conflicts
2019-07-06 Update lfops.c
    Fixed lf t55 reset
2019-07-07 Code cleaning
2019-07-11 update em4x05 timing (#846)
    See @mwalker33 issue #838
2019-07-18 Update cmdhfmf.c
    Support for 4K card sectors sizes
2019-07-23 Fix Issue #843 - hf mf chk - t Doesnt save to emulator memory
2019-08-01 Add an entry to CHANGELOG.md for NXP Originality Check
2019-08-01 'hf 14a apdu' improvement
    (PR 249 by @merlokk on https://github.com/RfidResearchGroup/proxmark3)
    * add option to print APDU (if it can be decoded)
    * add option to cconstruct extended and normal size APDUs
2019-08-10 add: 'hf mf personalize' (personalize UID on Mifare Classic EV1 7byte UID cards) * add/use some #defines * whitespace fixes * #include refactoring
2019-08-14 Remove space in long option
2019-08-22 PCF7931: Print found single/consecutive block(s), fixes to block 1 check
2019-08-25 add iclass.h
2019-09-02 'hf iclass loclass': fix error handling * fix handling of "BEING_CRACKED" flag * don't try to calculate KCus when some bytes couldn't be brute forced * whitespace fixes
2019-09-21 fix compile issue with gcc 9.1.0 (issue #868)
2019-09-29 fix 'hf iclass eload' (thanks to sherhannn79)
2019-10-07 fix iclass reader functions * remove unused CMD_ICLASS_READCHECK * fix wrong command coding in CodeIClassCommand() * switch field off at end of commands to avoid RDV4 overheating
2019-10-08 Update README.md
    Updated as per PR discussion thead
2019-10-27 fix 'hf iclass reader' and 'hf iclass readblk' * don't do READCHECK when not trying to authenticate * standard LED handling * remove unused FLAG_ICLASS_READER_ONLY_ONCE and FLAG_ICLASS_READER_ONE_TRY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
2019-11-08 mod 'hf list' * switch to argtable command line parsing (i.e. options must now be preceded by '-') * add option '-r' to display relative times * add option '-u' to display times in microseconds * fix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
2019-11-13 fix 'hf iclass snoop' * 'hf 15 snoop': determine and write meaningful times into trace
2019-11-25 Hitag fixes (#887)
    * don't display error message during 'lf search' when no Hitag tag is present
    * remove superfluous options in 'lf hitag read'
    * fix setting of default threshold when selecting FPGA_CMD_SET_EDGE_DETECT_THRESHOLD major mode
    * some refactoring
2019-12-04 fix 'hf iclass replay' (#888)
    * implement option -n for authentication with replayed NR/MAC pairs in 'dump' and 'readbl'
    * delete 'hf iclass replay'
2019-12-05 fix 'hf iclass chk' * Check for Credidt Keys as well * reduce authentication tries from 6 to 3 * correct text in 'hf iclass clone' for 'l' parameter * some reformatting and whitespace fixes
2019-12-09 fix 'hf iclass chk' (#894)
    * Check for Credidt Keys as well
    * reduce authentication tries from 6 to 3
    * correct text in 'hf iclass clone' for 'l' parameter
    * some reformatting and whitespace fixes
2019-12-18 add detection of static tag nonces
2019-12-18 remove 'not vulnerable to nested' error message
2019-12-19 more cleanup
2019-12-20 iso15693: decode WRITE_MULTI_BLOCK in 'hf list 15'
2019-12-23 speedup 'hf mf chk' * add separate timeout for tag response to nr_ar * measure response time and use it for response timeout * don't drop field between keyblocks * some reformatting * some whitespace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
2019-12-28 "hf mf ekeyprn d" doesn't works properly (#904)
    FIX: command "hf mf ekeyprn d" doesn't use the correct offset to locate the A key in data[] array and record the 2 last bytes followed by 4 0x00 instead of the 6 good bytes (All the A keys are corrup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
2019-12-29 fix gcc8 compiler warnings on string overflows
2020-01-07 fix hf search (#908)
    * fix memory access violation in HF14B_Other_Reader()
2020-01-10 appmain.c cleanup * reformatting * whitespace fixes * replace byte_t by uint8_t
2020-01-17 modify USB communications * use different data types for commands and responses * use variable length responses * maintain client/flasher compatibility with old format (e.g. when using old bootloader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
2020-01-27 uart_posix.c rework * added some LED handling in appmain.c (helped with debugging) * finally replaced the infamous device unlink by msleep(1000) * fixed some format strings in comms.c (with -DCOMMS_D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
2020-02-06 add a specific check function for static nonces in 'hf mf nested' * uses a fixed nr_enc and does all the crypto operations on client * for all possible keys calculate par_enc and ar_enc and send them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
2020-02-24 compatibility fix: get_clocktime() is not a available with older glibc
2020-03-16 fix 'hf mf perso' result feedback (#920)
2020-04-03 fixing iso15693 * NOISE_THRESHOLD /= 2 (starting with c41dd5f it became a relative threshold) * remove superfluous reader initialization
2020-04-09 update CI/.travis.yml (#929)
    * drop checks for MacOS 10.11 and 10.12
    * add checks for Ubuntu 16.04 and 18.04
    * add libnewlib-arm-none-eabi as prerequisite on Ubuntu
2020-05-11 Fix some printf/scanf format strings
2020-07-12 Add string.h
    Failed to compile without this line on MacOS Big Sur Beta.
2020-09-13 return an error when READBLOCK goes beyond tag size during emulation
2021-01-25 Avoid link error due to duplicate definition of blocknr in hitag.c and hitagS.c (#963)
2021-03-18 Fix gcc10 compiler warnings - update argtable3 to latest versions

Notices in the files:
armsrc/fpgaloader.c:
This code is licensed to you under the terms of the GNU GPL, version 2 or,
at your option, any later version. See the LICENSE.txt file for the text of
the license.
